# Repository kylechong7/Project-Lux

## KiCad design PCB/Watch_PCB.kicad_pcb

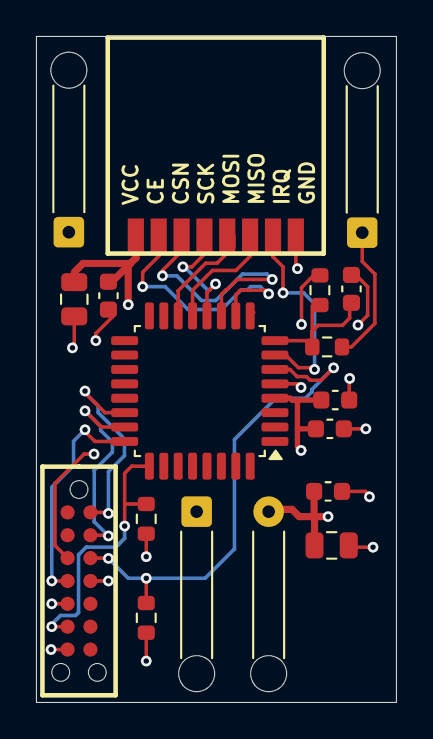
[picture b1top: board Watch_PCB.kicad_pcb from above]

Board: 4 copper layers, 20.0 x 37.0 mm, 17 parts (0 on the bottom side), 14 nets.

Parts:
1M1, 10k1, 10k2, 10k3: R; R_0603_1608Metric
1uF1, 4.7nF1, 100nF1, 100nF2, 100nF3: C; C_0603_1608Metric
4.7uF1, 22uF1: C; C_0805_2012Metric
J1: Conn_01x02_Pin; SolderWire-0.15sqmm_1x02_P4mm_D0.5mm_OD1.5mm_Relief
J2, J3: Conn_01x01_Pin; SolderWire-0.15sqmm_1x01_D0.5mm_OD1.5mm_Relief
J4: TC2070_-_Labelled; CONNECTOR_V1
U1: STM32G031K6Tx; LQFP-32_7x7mm_P0.8mm
U3: E01-ML01S

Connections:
+3.3V: 1uF1.2, 4.7uF1.2, 10k2.1, 22uF1.2, 100nF1.2, 100nF2.1, 100nF3.1, J1.2, J4.3 (T_VCC), U1.4 (VDD), U3.1 (VCC)
GND: 1M1.2, 1uF1.1, 4.7nF1.2, 4.7uF1.1, 10k3.1, 10k3.2, 22uF1.1, 100nF1.1, 100nF2.2, 100nF3.2, J1.1, J3.1, J4.5 (GND), J4.6 (T_JTDO/T_SWO), J4.7 (GND), J4.11 (GNDDETECT), U1.5 (VSS), U1.25 (PA14), U3.8 (GND)
unnamed: 10k1.1, J2.1
unnamed: 10k2.2, J4.12 (T_NRST), U1.6 (PF2)
unnamed: J4.13 (T_VCP_RX), U1.23 (PA10/PA12)
unnamed: J4.14 (T_VCP_TX), U1.22 (PA9/PA11)
unnamed: U1.7 (PA0), U3.7 (IRQ)
unnamed: 1M1.1, 4.7nF1.1, 10k1.2, U1.8 (PA1)
unnamed: U1.10 (PA3), U3.2 (CE)
unnamed: U1.11 (PA4), U3.3 (CSN)
unnamed: U1.12 (PA5), U3.4 (SCK)
unnamed: U1.13 (PA6), U3.6 (MISO)
unnamed: U1.14 (PA7), U3.5 (MOSI)
unnamed: J4.4, U1.24 (PA13)

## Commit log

2025-09-22 Create gerbers
2025-09-23 Create Amazon-Links
2025-09-23 Update and rename Amazon-Links to Links
2025-09-23 Create Description
2025-09-23 Rename Description to Preview
2025-09-23 Rename README.md to READ-ME/Preview
2025-09-23 Create READ-ME
2025-09-23 Rename READ-ME to README.md
2025-09-25 Create .stl files
2025-09-25 Create Receiver Module
2025-09-25 Create PCB Housing
2025-10-12 Create A_Overview.pdf
    This doc contains everything you need to know about Project Lux!
2025-10-12 Rename gerbers to Gerbers
2025-10-12 Create Temp
2025-10-12 Rename Project Lux.pdf to Project-Lux.pdf
2025-10-12 Rename Project-Lux.png to Project-Lux.png (Title page only)
2025-10-13 Rename click-me.png to cover-only.png
2025-10-13 Rename rx_main.c to main_rx.c
2025-10-13 Create ArduinoIDE
2025-10-13 Create Middleman Module
2025-10-13 Update Middleman Module
2025-10-16 Remove unused image link from README
2025-10-27 Update site link image in README
2025-10-27 Update link in README for project overview image
2025-10-27 Update link in README to point to PDF
2025-10-27 Fix link path for project overview image
2025-10-27 Update image link in README
2025-10-30 Rename Project-Lux (3).pdf to Project-Lux.pdf
